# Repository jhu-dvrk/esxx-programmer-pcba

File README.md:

# ESXX Programmer PCB

This repository contains the KiCad design files for the ESXX Programmer board (previously called ESPM Programmer). This board was originally developed to reprogram the FPGA on the ESPM board inside the PSM and ECM in the dVRK-Si system.

It is now also used to reprogram the FPGA on the ESSJ board inside the PSM and ECM setup joints in a full dVRK-Si system.

This board is connected to the JTAG port on the ESPM or ESSJ via a custom cable. Instructions for making the cable are in `dvrk-s-programmer-cable.pptx`.

The current firmware for this board is in [this repository](https://github.com/jhu-dvrk/esxx-programmer-firmware).  Previous versions (for ESPM Programmer) have been archived [here](https://github.com/jhu-dvrk/espm-programmer-firmware).

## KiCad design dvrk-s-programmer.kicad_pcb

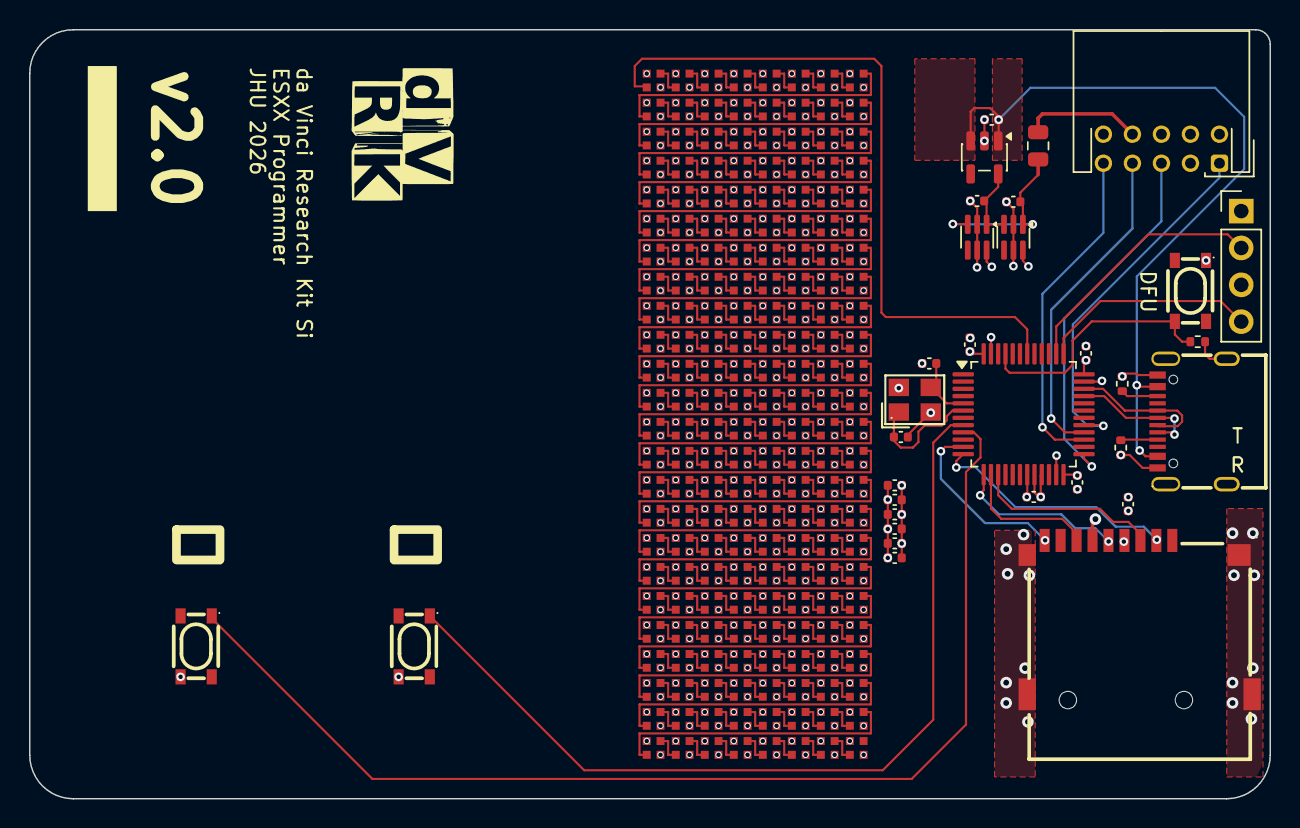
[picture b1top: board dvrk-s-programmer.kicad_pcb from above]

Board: 4 copper layers, 85.5 x 53.0 mm, 224 parts (0 on the bottom side), 218 nets.

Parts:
C1, C2: 10pf; C_0402_1005Metric
C3, C4, C6, C7, C10, C11, C12, C13, C14, C15, C16: 1uF; C_0402_1005Metric
C5, C8, C9: 1uf; C_0402_1005Metric
D3, D4, D5, D6, D7, D8, D9, D10, D11, D12, D13, D14, D15, D16, D17, D18, D19, D20, D21, D22, D23, D24, D25, D26, D27, D28, D29, D30, D31, D32, D33, D34, D35, D36, D37, D38, D39, D40, D41, D42, D43, D44, D45, D46, D47, D48, D49, D50, D51, D52, D53, D54, D55, D56, D57, D58, D59, D60, D61, D62, D63, D64, D65, D66, D67, D68, D69, D70, D71, D72, D73, D74, D75, D76, D77, D78, D79, D80, D81, D82, D83, D84, D85, D86, D87, D88, D89, D90, D91, D92, D93, D94, D95, D96, D97, D98, D99, D100, D101, D102, D103, D104, D105, D106, D107, D108, D109, D110, D111, D112, D113, D114, D115, D116, D117, D118, D119, D120, D121, D122, D123, D124, D125, D126, D127, D128, D129, D130, D131, D132, D133, D134, D135, D136, D137, D138, D139, D140, D141, D142, D143, D144, D145, D146, D147, D148, D149, D150, D151, D152, D153, D154, D155, D156, D157, D158, D159, D160, D161, D162, D163, D164, D165, D166, D167, D168, D169, D170, D171, D172, D173, D174, D175, D176, D177, D178, D179, D180, D181, D182, D183, D184, D185, D186, D187, D188, D189, D190, D191, D192, D193, D194: SK6805-EC15
F1: Polyfuse; Fuse_0805_2012Metric
J1: Conn_02x05_Odd_Even; JST_PHD_S10B-PHDSS_2x05_P2.00mm_Horizontal
J2: Conn_01x04; PinHeader_1x04_P2.54mm_Vertical
R1: 10k; R_0402_1005Metric
R4, R5: 5.1k; R_0402_1005Metric
U1: XKTF-015-N; TF-SMD_XKTF-015-N
U2, U8, U9: SKRPABE010; KEY-SMD_4P-L4.2-W3.2-P2.20-LS4.6
U3: STM32G474CETx; LQFP-48_7x7mm_P0.5mm
U4: USB-TYPE-C-019; TYPE-C-SMD_HX-TYPE-C-16PIN
U5: LP5907MFX-3.3; SOT-23-5
U6, U7: LM66100DCK; SOT-363_SC-70-6
X1: L327S080D11L; CRYSTAL-SMD_4P-L3.2-W2.5-BL

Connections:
/BOOT0: R1.2, U2.4, U3.45 (PB8)
/CS: U1.2 (CD/DAT3), U3.12 (PA4)
/LED: D3.1 (DIN), U3.42 (PB5)
/MISO: U1.7 (DAT0), U3.14 (PA6)
/MOSI: U1.3 (CMD), U3.15 (PA7)
/SCK: U1.5 (CLK), U3.13 (PA5)
/SWCLK: J2.2, U3.38 (PA14)
/SWDIO: J2.4, U3.37 (PA13)
/TARGET_3.3: C8.2, F1.2, U6.1 (VIN), U7.3 (~CE)
/TCK: J1.9, U3.27 (PB13)
/TDI: J1.1, U3.29 (PB15)
/TDO: J1.7, U3.28 (PB14)
/TMS: J1.5, U3.25 (PB11)
/USB_3.3: C9.2, U5.5 (OUT), U6.3 (~CE), U7.1 (VIN)
/button_go: U3.9 (PA1), U9.1
/button_next: U3.8 (PA0), U8.1
/card_detect: U1.9 (CD), U3.11 (PA3)
/d+: U3.34 (PA12), U4.A6, U4.B6
/d-: U3.33 (PA11), U4.A7, U4.B7
GND: C1.1, C2.1, C3.2, C4.2, C5.1, C6.2, C7.2, C8.1, C9.1, C10.2, C11.2, C12.2, C13.2, C14.2, C15.2, C16.2, D3.4 (VSS), D4.4 (VSS), D5.4 (VSS), D6.4 (VSS), D7.4 (VSS), D8.4 (VSS), D9.4 (VSS), D10.4 (VSS), D11.4 (VSS), D12.4 (VSS), D13.4 (VSS), D14.4 (VSS), D15.4 (VSS), D16.4 (VSS), D17.4 (VSS), D18.4 (VSS), D19.4 (VSS), D20.4 (VSS), D21.4 (VSS), D22.4 (VSS), D23.4 (VSS), D24.4 (VSS), D25.4 (VSS), D26.4 (VSS), D27.4 (VSS), D28.4 (VSS), D29.4 (VSS), D30.4 (VSS), D31.4 (VSS), D32.4 (VSS), D33.4 (VSS), D34.4 (VSS), D35.4 (VSS), D36.4 (VSS), D37.4 (VSS), D38.4 (VSS), D39.4 (VSS), D40.4 (VSS), D41.4 (VSS), D42.4 (VSS), D43.4 (VSS), D44.4 (VSS), D45.4 (VSS), D46.4 (VSS), D47.4 (VSS), D48.4 (VSS), D49.4 (VSS), D50.4 (VSS), D51.4 (VSS), D52.4 (VSS), D53.4 (VSS), D54.4 (VSS), D55.4 (VSS), D56.4 (VSS), D57.4 (VSS), D58.4 (VSS), D59.4 (VSS), D60.4 (VSS), D61.4 (VSS), D62.4 (VSS), D63.4 (VSS), D64.4 (VSS), D65.4 (VSS), D66.4 (VSS), D67.4 (VSS), D68.4 (VSS), D69.4 (VSS), D70.4 (VSS), D71.4 (VSS), D72.4 (VSS), D73.4 (VSS), D74.4 (VSS), D75.4 (VSS), D76.4 (VSS), D77.4 (VSS), D78.4 (VSS), D79.4 (VSS), D80.4 (VSS), D81.4 (VSS), D82.4 (VSS), D83.4 (VSS), D84.4 (VSS), D85.4 (VSS), D86.4 (VSS), D87.4 (VSS), D88.4 (VSS), D89.4 (VSS), D90.4 (VSS), D91.4 (VSS), D92.4 (VSS), D93.4 (VSS), D94.4 (VSS), D95.4 (VSS), D96.4 (VSS), D97.4 (VSS), D98.4 (VSS), D99.4 (VSS), D100.4 (VSS), D101.4 (VSS), D102.4 (VSS), D103.4 (VSS), D104.4 (VSS), D105.4 (VSS), D106.4 (VSS), D107.4 (VSS), D108.4 (VSS), D109.4 (VSS), D110.4 (VSS), D111.4 (VSS), D112.4 (VSS), D113.4 (VSS), D114.4 (VSS), D115.4 (VSS), D116.4 (VSS), D117.4 (VSS), D118.4 (VSS), D119.4 (VSS), D120.4 (VSS), D121.4 (VSS), D122.4 (VSS), D123.4 (VSS), D124.4 (VSS), D125.4 (VSS), D126.4 (VSS), D127.4 (VSS), D128.4 (VSS), D129.4 (VSS), D130.4 (VSS), D131.4 (VSS), D132.4 (VSS), D133.4 (VSS), D134.4 (VSS), D135.4 (VSS), D136.4 (VSS), D137.4 (VSS), D138.4 (VSS), D139.4 (VSS), D140.4 (VSS), D141.4 (VSS), D142.4 (VSS), D143.4 (VSS), D144.4 (VSS), D145.4 (VSS), D146.4 (VSS), D147.4 (VSS), D148.4 (VSS), D149.4 (VSS), D150.4 (VSS), D151.4 (VSS), D152.4 (VSS), D153.4 (VSS), D154.4 (VSS), D155.4 (VSS), D156.4 (VSS), D157.4 (VSS), D158.4 (VSS), D159.4 (VSS), D160.4 (VSS), D161.4 (VSS), D162.4 (VSS), D163.4 (VSS), D164.4 (VSS), D165.4 (VSS), D166.4 (VSS), D167.4 (VSS), D168.4 (VSS), D169.4 (VSS), D170.4 (VSS), D171.4 (VSS), D172.4 (VSS), D173.4 (VSS), D174.4 (VSS), D175.4 (VSS), D176.4 (VSS), D177.4 (VSS), D178.4 (VSS), D179.4 (VSS), D180.4 (VSS), D181.4 (VSS), D182.4 (VSS), D183.4 (VSS), D184.4 (VSS), D185.4 (VSS), D186.4 (VSS), D187.4 (VSS), D188.4 (VSS), D189.4 (VSS), D190.4 (VSS), D191.4 (VSS), D192.4 (VSS), D193.4 (VSS), D194.4 (VSS), J1.10, J2.3, R1.1, R4.2, R5.2, U1.6 (VSS), U1.10 (GND), U1.11 (GND), U1.12 (GND), U1.13 (GND), U3.19 (VSSA), U3.23 (VSS), U3.35 (VSS), U3.47 (VSS), U4.1, U4.A1, U4.A12, U5.2 (GND), U6.2 (GND), U6.5 (ST), U7.2 (GND), U7.5 (ST), U8.4, U9.4, X1.2 (GND), X1.4 (GND)
unnamed: D10.1 (DIN), D177.3 (DOUT)
unnamed: D10.3 (DOUT), D34.1 (DIN)
unnamed: D11.1 (DIN), D178.3 (DOUT)
unnamed: D11.3 (DOUT), D35.1 (DIN)
unnamed: D12.1 (DIN), D179.3 (DOUT)
unnamed: D12.3 (DOUT), D36.1 (DIN)
unnamed: D13.1 (DIN), D180.3 (DOUT)
unnamed: D13.3 (DOUT), D37.1 (DIN)
unnamed: D14.1 (DIN), D181.3 (DOUT)
unnamed: D14.3 (DOUT), D38.1 (DIN)
unnamed: D15.1 (DIN), D182.3 (DOUT)
unnamed: D15.3 (DOUT), D39.1 (DIN)
unnamed: D16.1 (DIN), D183.3 (DOUT)
unnamed: D16.3 (DOUT), D40.1 (DIN)
unnamed: D17.1 (DIN), D184.3 (DOUT)
unnamed: D17.3 (DOUT), D41.1 (DIN)
unnamed: D18.1 (DIN), D185.3 (DOUT)
unnamed: D18.3 (DOUT), D42.1 (DIN)
unnamed: D19.3 (DOUT), D43.1 (DIN)
unnamed: D20.3 (DOUT), D44.1 (DIN)
unnamed: D21.3 (DOUT), D45.1 (DIN)
unnamed: D22.3 (DOUT), D46.1 (DIN)
unnamed: D23.3 (DOUT), D47.1 (DIN)
unnamed: D24.3 (DOUT), D48.1 (DIN)
unnamed: D25.3 (DOUT), D49.1 (DIN)
unnamed: D26.3 (DOUT), D50.1 (DIN)
unnamed: D3.3 (DOUT), D27.1 (DIN)
unnamed: D27.3 (DOUT), D51.1 (DIN)
unnamed: D4.3 (DOUT), D28.1 (DIN)
unnamed: D28.3 (DOUT), D52.1 (DIN)
unnamed: D5.3 (DOUT), D29.1 (DIN)
unnamed: D29.3 (DOUT), D53.1 (DIN)
unnamed: D6.3 (DOUT), D30.1 (DIN)
unnamed: D30.3 (DOUT), D54.1 (DIN)
unnamed: D7.3 (DOUT), D31.1 (DIN)
unnamed: D31.3 (DOUT), D55.1 (DIN)
unnamed: D8.3 (DOUT), D32.1 (DIN)
unnamed: D32.3 (DOUT), D56.1 (DIN)
unnamed: D9.3 (DOUT), D33.1 (DIN)
unnamed: D33.3 (DOUT), D57.1 (DIN)
unnamed: D34.3 (DOUT), D58.1 (DIN)
unnamed: D35.3 (DOUT), D59.1 (DIN)
unnamed: D36.3 (DOUT), D60.1 (DIN)
unnamed: D37.3 (DOUT), D61.1 (DIN)
unnamed: D38.3 (DOUT), D62.1 (DIN)
unnamed: D39.3 (DOUT), D63.1 (DIN)
unnamed: D40.3 (DOUT), D64.1 (DIN)
unnamed: D41.3 (DOUT), D65.1 (DIN)
unnamed: D42.3 (DOUT), D66.1 (DIN)
unnamed: D43.3 (DOUT), D67.1 (DIN)
unnamed: D44.3 (DOUT), D68.1 (DIN)
unnamed: D45.3 (DOUT), D69.1 (DIN)
unnamed: D46.3 (DOUT), D70.1 (DIN)
unnamed: D47.3 (DOUT), D71.1 (DIN)
unnamed: D48.3 (DOUT), D72.1 (DIN)
unnamed: D49.3 (DOUT), D73.1 (DIN)
unnamed: D50.3 (DOUT), D74.1 (DIN)
unnamed: D51.3 (DOUT), D75.1 (DIN)
unnamed: D52.3 (DOUT), D76.1 (DIN)
unnamed: D53.3 (DOUT), D77.1 (DIN)
unnamed: D54.3 (DOUT), D78.1 (DIN)
unnamed: D55.3 (DOUT), D79.1 (DIN)
unnamed: D56.3 (DOUT), D80.1 (DIN)
unnamed: D57.3 (DOUT), D81.1 (DIN)
unnamed: D58.3 (DOUT), D82.1 (DIN)
unnamed: D59.3 (DOUT), D83.1 (DIN)
unnamed: D60.3 (DOUT), D84.1 (DIN)
unnamed: D61.3 (DOUT), D85.1 (DIN)
unnamed: D62.3 (DOUT), D86.1 (DIN)
unnamed: D63.3 (DOUT), D87.1 (DIN)
unnamed: D64.3 (DOUT), D88.1 (DIN)
unnamed: D65.3 (DOUT), D89.1 (DIN)
unnamed: D66.3 (DOUT), D90.1 (DIN)
unnamed: D67.3 (DOUT), D91.1 (DIN)
unnamed: D68.3 (DOUT), D92.1 (DIN)
unnamed: D69.3 (DOUT), D93.1 (DIN)
unnamed: D70.3 (DOUT), D94.1 (DIN)
unnamed: D71.3 (DOUT), D95.1 (DIN)
unnamed: D72.3 (DOUT), D96.1 (DIN)
unnamed: D73.3 (DOUT), D97.1 (DIN)
unnamed: D74.3 (DOUT), D98.1 (DIN)
unnamed: D75.3 (DOUT), D99.1 (DIN)
unnamed: D76.3 (DOUT), D100.1 (DIN)
unnamed: D100.3 (DOUT), D124.1 (DIN)
unnamed: D77.3 (DOUT), D101.1 (DIN)
unnamed: D101.3 (DOUT), D125.1 (DIN)
unnamed: D78.3 (DOUT), D102.1 (DIN)
unnamed: D102.3 (DOUT), D126.1 (DIN)
unnamed: D79.3 (DOUT), D103.1 (DIN)
unnamed: D103.3 (DOUT), D127.1 (DIN)
unnamed: D80.3 (DOUT), D104.1 (DIN)
unnamed: D104.3 (DOUT), D128.1 (DIN)
unnamed: D81.3 (DOUT), D105.1 (DIN)
unnamed: D105.3 (DOUT), D129.1 (DIN)
unnamed: D82.3 (DOUT), D106.1 (DIN)
unnamed: D106.3 (DOUT), D130.1 (DIN)
unnamed: D83.3 (DOUT), D107.1 (DIN)
unnamed: D107.3 (DOUT), D131.1 (DIN)
unnamed: D84.3 (DOUT), D108.1 (DIN)
unnamed: D108.3 (DOUT), D132.1 (DIN)
unnamed: D85.3 (DOUT), D109.1 (DIN)
unnamed: D109.3 (DOUT), D133.1 (DIN)
unnamed: D86.3 (DOUT), D110.1 (DIN)
unnamed: D110.3 (DOUT), D134.1 (DIN)
unnamed: D87.3 (DOUT), D111.1 (DIN)
unnamed: D111.3 (DOUT), D135.1 (DIN)
unnamed: D88.3 (DOUT), D112.1 (DIN)
unnamed: D112.3 (DOUT), D136.1 (DIN)
unnamed: D89.3 (DOUT), D113.1 (DIN)
unnamed: D113.3 (DOUT), D137.1 (DIN)
unnamed: D90.3 (DOUT), D114.1 (DIN)
unnamed: D114.3 (DOUT), D138.1 (DIN)
unnamed: D91.3 (DOUT), D115.1 (DIN)
unnamed: D115.3 (DOUT), D139.1 (DIN)
unnamed: D92.3 (DOUT), D116.1 (DIN)
unnamed: D116.3 (DOUT), D140.1 (DIN)
unnamed: D93.3 (DOUT), D117.1 (DIN)
unnamed: D117.3 (DOUT), D141.1 (DIN)
unnamed: D94.3 (DOUT), D118.1 (DIN)
unnamed: D118.3 (DOUT), D142.1 (DIN)
unnamed: D95.3 (DOUT), D119.1 (DIN)
unnamed: D119.3 (DOUT), D143.1 (DIN)
unnamed: D96.3 (DOUT), D120.1 (DIN)
unnamed: D120.3 (DOUT), D144.1 (DIN)
unnamed: D97.3 (DOUT), D121.1 (DIN)
unnamed: D121.3 (DOUT), D145.1 (DIN)
unnamed: D98.3 (DOUT), D122.1 (DIN)
unnamed: D122.3 (DOUT), D146.1 (DIN)
unnamed: D99.3 (DOUT), D123.1 (DIN)
unnamed: D123.3 (DOUT), D147.1 (DIN)
unnamed: D124.3 (DOUT), D148.1 (DIN)
unnamed: D125.3 (DOUT), D149.1 (DIN)
unnamed: D126.3 (DOUT), D150.1 (DIN)
unnamed: D127.3 (DOUT), D151.1 (DIN)
unnamed: D128.3 (DOUT), D152.1 (DIN)
unnamed: D129.3 (DOUT), D153.1 (DIN)
unnamed: D130.3 (DOUT), D154.1 (DIN)
unnamed: D131.3 (DOUT), D155.1 (DIN)
unnamed: D132.3 (DOUT), D156.1 (DIN)
unnamed: D133.3 (DOUT), D157.1 (DIN)
unnamed: D134.3 (DOUT), D158.1 (DIN)
unnamed: D135.3 (DOUT), D159.1 (DIN)
unnamed: D136.3 (DOUT), D160.1 (DIN)
unnamed: D137.3 (DOUT), D161.1 (DIN)
unnamed: D138.3 (DOUT), D162.1 (DIN)
unnamed: D139.3 (DOUT), D163.1 (DIN)
unnamed: D140.3 (DOUT), D164.1 (DIN)
unnamed: D141.3 (DOUT), D165.1 (DIN)
unnamed: D142.3 (DOUT), D166.1 (DIN)
unnamed: D143.3 (DOUT), D167.1 (DIN)
unnamed: D144.3 (DOUT), D168.1 (DIN)
unnamed: D145.3 (DOUT), D169.1 (DIN)
unnamed: D146.3 (DOUT), D170.1 (DIN)
unnamed: D147.3 (DOUT), D171.1 (DIN)
unnamed: D148.3 (DOUT), D172.1 (DIN)
unnamed: D149.3 (DOUT), D173.1 (DIN)
unnamed: D150.3 (DOUT), D174.1 (DIN)
unnamed: D151.3 (DOUT), D175.1 (DIN)
unnamed: D152.3 (DOUT), D176.1 (DIN)
unnamed: D153.3 (DOUT), D177.1 (DIN)
unnamed: D154.3 (DOUT), D178.1 (DIN)
unnamed: D155.3 (DOUT), D179.1 (DIN)
unnamed: D156.3 (DOUT), D180.1 (DIN)
unnamed: D157.3 (DOUT), D181.1 (DIN)
unnamed: D158.3 (DOUT), D182.1 (DIN)
unnamed: D159.3 (DOUT), D183.1 (DIN)
unnamed: D160.3 (DOUT), D184.1 (DIN)
unnamed: D161.3 (DOUT), D185.1 (DIN)
unnamed: D162.3 (DOUT), D186.1 (DIN)
unnamed: D163.3 (DOUT), D187.1 (DIN)
unnamed: D164.3 (DOUT), D188.1 (DIN)
unnamed: D165.3 (DOUT), D189.1 (DIN)
unnamed: D166.3 (DOUT), D190.1 (DIN)
unnamed: D167.3 (DOUT), D191.1 (DIN)
unnamed: D168.3 (DOUT), D192.1 (DIN)
unnamed: D169.3 (DOUT), D193.1 (DIN)
unnamed: D170.3 (DOUT), D194.1 (DIN)
unnamed: D4.1 (DIN), D171.3 (DOUT)
unnamed: D5.1 (DIN), D172.3 (DOUT)
unnamed: D6.1 (DIN), D173.3 (DOUT)
unnamed: D7.1 (DIN), D174.3 (DOUT)
unnamed: D8.1 (DIN), D175.3 (DOUT)
unnamed: D9.1 (DIN), D176.3 (DOUT)
unnamed: D19.1 (DIN), D186.3 (DOUT)
unnamed: D20.1 (DIN), D187.3 (DOUT)
unnamed: D21.1 (DIN), D188.3 (DOUT)
unnamed: D22.1 (DIN), D189.3 (DOUT)
unnamed: D23.1 (DIN), D190.3 (DOUT)
unnamed: D24.1 (DIN), D191.3 (DOUT)
unnamed: D25.1 (DIN), D192.3 (DOUT)
unnamed: D26.1 (DIN), D193.3 (DOUT)
unnamed: F1.1, J1.8
unnamed: R4.1, U4.B5
unnamed: R5.1, U4.A5
unnamed: C1.2, U3.5 (PF0), X1.3
unnamed: C2.2, U3.6 (PF1), X1.1
VBUS: C5.2, U4.A4, U4.A9, U5.1 (IN), U5.3 (EN)
VDD: C3.1, C4.1, C6.1, C7.1, C10.1, C11.1, C12.1, C13.1, C14.1, C15.1, C16.1, D3.2 (VDD), D4.2 (VDD), D5.2 (VDD), D6.2 (VDD), D7.2 (VDD), D8.2 (VDD), D9.2 (VDD), D10.2 (VDD), D11.2 (VDD), D12.2 (VDD), D13.2 (VDD), D14.2 (VDD), D15.2 (VDD), D16.2 (VDD), D17.2 (VDD), D18.2 (VDD), D19.2 (VDD), D20.2 (VDD), D21.2 (VDD), D22.2 (VDD), D23.2 (VDD), D24.2 (VDD), D25.2 (VDD), D26.2 (VDD), D27.2 (VDD), D28.2 (VDD), D29.2 (VDD), D30.2 (VDD), D31.2 (VDD), D32.2 (VDD), D33.2 (VDD), D34.2 (VDD), D35.2 (VDD), D36.2 (VDD), D37.2 (VDD), D38.2 (VDD), D39.2 (VDD), D40.2 (VDD), D41.2 (VDD), D42.2 (VDD), D43.2 (VDD), D44.2 (VDD), D45.2 (VDD), D46.2 (VDD), D47.2 (VDD), D48.2 (VDD), D49.2 (VDD), D50.2 (VDD), D51.2 (VDD), D52.2 (VDD), D53.2 (VDD), D54.2 (VDD), D55.2 (VDD), D56.2 (VDD), D57.2 (VDD), D58.2 (VDD), D59.2 (VDD), D60.2 (VDD), D61.2 (VDD), D62.2 (VDD), D63.2 (VDD), D64.2 (VDD), D65.2 (VDD), D66.2 (VDD), D67.2 (VDD), D68.2 (VDD), D69.2 (VDD), D70.2 (VDD), D71.2 (VDD), D72.2 (VDD), D73.2 (VDD), D74.2 (VDD), D75.2 (VDD), D76.2 (VDD), D77.2 (VDD), D78.2 (VDD), D79.2 (VDD), D80.2 (VDD), D81.2 (VDD), D82.2 (VDD), D83.2 (VDD), D84.2 (VDD), D85.2 (VDD), D86.2 (VDD), D87.2 (VDD), D88.2 (VDD), D89.2 (VDD), D90.2 (VDD), D91.2 (VDD), D92.2 (VDD), D93.2 (VDD), D94.2 (VDD), D95.2 (VDD), D96.2 (VDD), D97.2 (VDD), D98.2 (VDD), D99.2 (VDD), D100.2 (VDD), D101.2 (VDD), D102.2 (VDD), D103.2 (VDD), D104.2 (VDD), D105.2 (VDD), D106.2 (VDD), D107.2 (VDD), D108.2 (VDD), D109.2 (VDD), D110.2 (VDD), D111.2 (VDD), D112.2 (VDD), D113.2 (VDD), D114.2 (VDD), D115.2 (VDD), D116.2 (VDD), D117.2 (VDD), D118.2 (VDD), D119.2 (VDD), D120.2 (VDD), D121.2 (VDD), D122.2 (VDD), D123.2 (VDD), D124.2 (VDD), D125.2 (VDD), D126.2 (VDD), D127.2 (VDD), D128.2 (VDD), D129.2 (VDD), D130.2 (VDD), D131.2 (VDD), D132.2 (VDD), D133.2 (VDD), D134.2 (VDD), D135.2 (VDD), D136.2 (VDD), D137.2 (VDD), D138.2 (VDD), D139.2 (VDD), D140.2 (VDD), D141.2 (VDD), D142.2 (VDD), D143.2 (VDD), D144.2 (VDD), D145.2 (VDD), D146.2 (VDD), D147.2 (VDD), D148.2 (VDD), D149.2 (VDD), D150.2 (VDD), D151.2 (VDD), D152.2 (VDD), D153.2 (VDD), D154.2 (VDD), D155.2 (VDD), D156.2 (VDD), D157.2 (VDD), D158.2 (VDD), D159.2 (VDD), D160.2 (VDD), D161.2 (VDD), D162.2 (VDD), D163.2 (VDD), D164.2 (VDD), D165.2 (VDD), D166.2 (VDD), D167.2 (VDD), D168.2 (VDD), D169.2 (VDD), D170.2 (VDD), D171.2 (VDD), D172.2 (VDD), D173.2 (VDD), D174.2 (VDD), D175.2 (VDD), D176.2 (VDD), D177.2 (VDD), D178.2 (VDD), D179.2 (VDD), D180.2 (VDD), D181.2 (VDD), D182.2 (VDD), D183.2 (VDD), D184.2 (VDD), D185.2 (VDD), D186.2 (VDD), D187.2 (VDD), D188.2 (VDD), D189.2 (VDD), D190.2 (VDD), D191.2 (VDD), D192.2 (VDD), D193.2 (VDD), D194.2 (VDD), J2.1, U1.4 (VDD), U2.1, U3.20 (VREF+), U3.21 (VDDA), U3.24 (VDD), U3.36 (VDD), U3.48 (VDD), U6.6 (VOUT), U7.6 (VOUT)

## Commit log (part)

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2025-09-08 Added README and programmer cable documentation
2026-03-17 changed mcu. added usb.
2026-03-26 added led array. changed microcontroller.
